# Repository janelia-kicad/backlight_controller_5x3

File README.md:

- [Repository Information](#orge3a2ecc)
  - [Description](#org1a124a6)
- [Images](#orgde4a8eb)
- [Schematic](#org565d04b)
- [Gerbers](#orgdefb019)
- [Bill of Materials](#orgbfc12b0)
  - [PCB Parts](#org35e0f28)
  - [Supplemental Parts](#orgb5c14fe)
  - [Vendor Parts Lists](#org5ae73cf)
- [Supplemental Documentation](#orgd3afd80)
  - [Assembly Instructions](#orgc67ada5)
- [Manufacturing Archive](#org51454f0)

# Repository Information

-   **Name:** backlight\_controller\_5x3
-   **Version:** 1.3
-   **License:** Open-Source Hardware
-   **URL:** <https://github.com/janelia-kicad/backlight_controller_5x3>
-   **Author:** Peter Polidoro
-   **Email:** peter@polidoro.io

## Description

This board controls up to four Smart Vision backlights with IR and visible channels plus additional high and low power channel outputs.

# Images

# Schematic

[./schematic/backlight\_controller\_5x3.pdf](./schematic/backlight_controller_5x3.pdf)

# Gerbers

# Bill of Materials

## PCB Parts

| Item | Reference(s)                                                | Quantity | Manufacturer Part Number | Description                                                       |
|---- |----------------------------------------------------------- |-------- |------------------------ |----------------------------------------------------------------- |
| 1    | C1 C2 C3 C4 C5 C6                                           | 6        | C0805T104K5RAL7800       | CAP CER 0.1UF 50V X7R                                             |
| 2    | D1                                                          | 1        | PMEG045V100EPDZ          | DIODE SCHOTTKY 45V 10A                                            |
| 3    | D10 D11 D12 D13 D14 D15 D16 D17 D18 D2 D3 D4 D5 D6 D7 D8 D9 | 17       | LTST-C170GKT             | LED GREEN CLEAR SMD                                               |
| 4    | HPS1 HPS2 HPS3 HPS4                                         | 4        | BTS3256DAUMA1            | IC SWITCH SMART LOWSIDE                                           |
| 5    | J1 J2                                                       | 2        | PBC25SAAN                | CONN HEADER VERT 25POS 2.54MM                                     |
| 6    | J10 J11 J12 J5 J6 J7 J8 J9                                  | 8        | 1411976                  | CONN FMALE INSERT 5POS SOLDER                                     |
| 7    | J3                                                          | 1        | 09551156612741           | CONN D-SUB RCPT 9POS SMD SOLDER                                   |
| 8    | J4                                                          | 1        | 09551296812741           | CONN D-SUB PLUG 9POS SMD SOLDER                                   |
| 9    | P1                                                          | 1        | 0039301060               | CONN HEADER 6POS 4.2MM R/A TIN                                    |
| 10   | R1                                                          | 1        | ERJ-6ENF2201V            | RES SMD 2.2K OHM 1% 1/8W                                          |
| 11   | R10 R12 R14 R16 R18 R19 R2 R20 R21 R22 R23 R24 R25 R4 R6 R8 | 16       | ERJ-6ENF2870V            | RES SMD 287 OHM 1% 1/8W                                           |
| 12   | R11 R13 R15 R17                                             | 4        | ERJ-6ENF75R0V            | RES SMD 75 OHM 1% 1/8W                                            |
| 13   | R3 R5 R7 R9                                                 | 4        | ERJ-6ENF5901V            | RES SMD 5.9K OHM 1% 1/8W                                          |
| 14   | U1 U2                                                       | 2        | SN74ABT541BDWR           | Buffer Non-Inverting 1 Element 8 Bit per Element Push-Pull Output |
| 15   | U10 U3 U4 U5 U6 U7 U8 U9                                    | 8        | NUD3124LT1G              | IC INDCT LOAD DRVR AUTO                                           |

## Supplemental Parts

| Item | Quantity | Manufacturer Part Number   | Description                    |
|---- |-------- |-------------------------- |------------------------------ |
| 1    | 1        | GST280A24-C6P              | AC/DC DESKTOP ADAPTER 24V 280W |
| 2    | 1        | CORD IEC 320-C13 6FT BLACK | CORD IEC 320-C13 6FT BLACK     |

## Vendor Parts Lists

[./bom/Digi-Key\_parts.csv](./bom/Digi-Key_parts.csv)

[./bom/supplemental\_Digi-Key\_parts.csv](./bom/supplemental_Digi-Key_parts.csv)

# Supplemental Documentation

## Assembly Instructions

-   Solder surface mount and through hole components onto the pcb.

# Manufacturing Archive

Send manufacturing zip file to your favorite PCB manufacturer for fabrication.

[./manufacturing/backlight\_controller\_5x3\_v1.3.zip](./manufacturing/backlight_controller_5x3_v1.3.zip)

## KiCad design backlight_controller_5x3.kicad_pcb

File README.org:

# Created 2019-05-20 Mon 15:17
#+OPTIONS: title:nil author:nil email:nil toc:t |:t ^:nil
* Repository Information

- Name :: backlight_controller_5x3
- Version :: 1.3
- License :: Open-Source Hardware
- URL :: https://github.com/janelia-kicad/backlight_controller_5x3
- Author :: Peter Polidoro
- Email :: peter@polidoro.io

** Description

This board controls up to four Smart Vision backlights with IR and visible
channels plus additional high and low power channel outputs.

* Images

[[file:./images/top.png]]

[[file:./images/bottom.png]]

* Schematic

[[file:./schematic/backlight_controller_5x3.pdf][./schematic/backlight_controller_5x3.pdf]]

[[file:./schematic/images/schematic00.png]]

[[file:./schematic/images/schematic01.png]]

[[file:./schematic/images/schematic02.png]]

[[file:./schematic/images/schematic03.png]]

[[file:./schematic/images/schematic04.png]]

[[file:./schematic/images/schematic05.png]]

[[file:./schematic/images/schematic06.png]]

[[file:./schematic/images/schematic07.png]]

[[file:./schematic/images/schematic08.png]]

[[file:./schematic/images/schematic09.png]]

[[file:./schematic/images/schematic10.png]]

[[file:./schematic/images/schematic11.png]]

[[file:./schematic/images/schematic12.png]]

[[file:./schematic/images/schematic13.png]]

[[file:./schematic/images/schematic14.png]]

[[file:./schematic/images/schematic15.png]]

[[file:./schematic/images/schematic16.png]]

[[file:./schematic/images/schematic17.png]]

[[file:./schematic/images/schematic18.png]]

[[file:./schematic/images/schematic19.png]]

[[file:./schematic/images/schematic20.png]]

[[file:./schematic/images/schematic21.png]]

* Gerbers

[[file:./gerbers/images/gerbers00.png]]

[[file:./gerbers/images/gerbers01.png]]

* Bill of Materials

** PCB Parts

| Item | Reference(s)                                                | Quantity | Manufacturer Part Number | Description                                                       |
|------+-------------------------------------------------------------+----------+--------------------------+-------------------------------------------------------------------|
|    1 | C1 C2 C3 C4 C5 C6                                           |        6 | C0805T104K5RAL7800       | CAP CER 0.1UF 50V X7R                                             |
|    2 | D1                                                          |        1 | PMEG045V100EPDZ          | DIODE SCHOTTKY 45V 10A                                            |
|    3 | D10 D11 D12 D13 D14 D15 D16 D17 D18 D2 D3 D4 D5 D6 D7 D8 D9 |       17 | LTST-C170GKT             | LED GREEN CLEAR SMD                                               |
|    4 | HPS1 HPS2 HPS3 HPS4                                         |        4 | BTS3256DAUMA1            | IC SWITCH SMART LOWSIDE                                           |
|    5 | J1 J2                                                       |        2 | PBC25SAAN                | CONN HEADER VERT 25POS 2.54MM                                     |
|    6 | J10 J11 J12 J5 J6 J7 J8 J9                                  |        8 | 1411976                  | CONN FMALE INSERT 5POS SOLDER                                     |
|    7 | J3                                                          |        1 | 09551156612741           | CONN D-SUB RCPT 9POS SMD SOLDER                                   |
|    8 | J4                                                          |        1 | 09551296812741           | CONN D-SUB PLUG 9POS SMD SOLDER                                   |
|    9 | P1                                                          |        1 | 0039301060               | CONN HEADER 6POS 4.2MM R/A TIN                                    |
|   10 | R1                                                          |        1 | ERJ-6ENF2201V            | RES SMD 2.2K OHM 1% 1/8W                                          |
|   11 | R10 R12 R14 R16 R18 R19 R2 R20 R21 R22 R23 R24 R25 R4 R6 R8 |       16 | ERJ-6ENF2870V            | RES SMD 287 OHM 1% 1/8W                                           |
|   12 | R11 R13 R15 R17                                             |        4 | ERJ-6ENF75R0V            | RES SMD 75 OHM 1% 1/8W                                            |
|   13 | R3 R5 R7 R9                                                 |        4 | ERJ-6ENF5901V            | RES SMD 5.9K OHM 1% 1/8W                                          |
|   14 | U1 U2                                                       |        2 | SN74ABT541BDWR           | Buffer Non-Inverting 1 Element 8 Bit per Element Push-Pull Output |
|   15 | U10 U3 U4 U5 U6 U7 U8 U9                                    |        8 | NUD3124LT1G              | IC INDCT LOAD DRVR AUTO                                           |

** Supplemental Parts

| Item | Quantity | Manufacturer Part Number   | Description                    |
|------+----------+----------------------------+--------------------------------|
|    1 |        1 | GST280A24-C6P              | AC/DC DESKTOP ADAPTER 24V 280W |
|    2 |        1 | CORD IEC 320-C13 6FT BLACK | CORD IEC 320-C13 6FT BLACK     |

** Vendor Parts Lists

[[file:./bom/Digi-Key_parts.csv][./bom/Digi-Key_parts.csv]]

[[file:./bom/supplemental_Digi-Key_parts.csv][./bom/supplemental_Digi-Key_parts.csv]]

* Supplemental Documentation

** Assembly Instructions

- Solder surface mount and through hole components onto the pcb.

* Manufacturing Archive

Send manufacturing zip file to your favorite PCB manufacturer for fabrication.

[[file:./manufacturing/backlight_controller_5x3_v1.3.zip][./manufacturing/backlight_controller_5x3_v1.3.zip]]

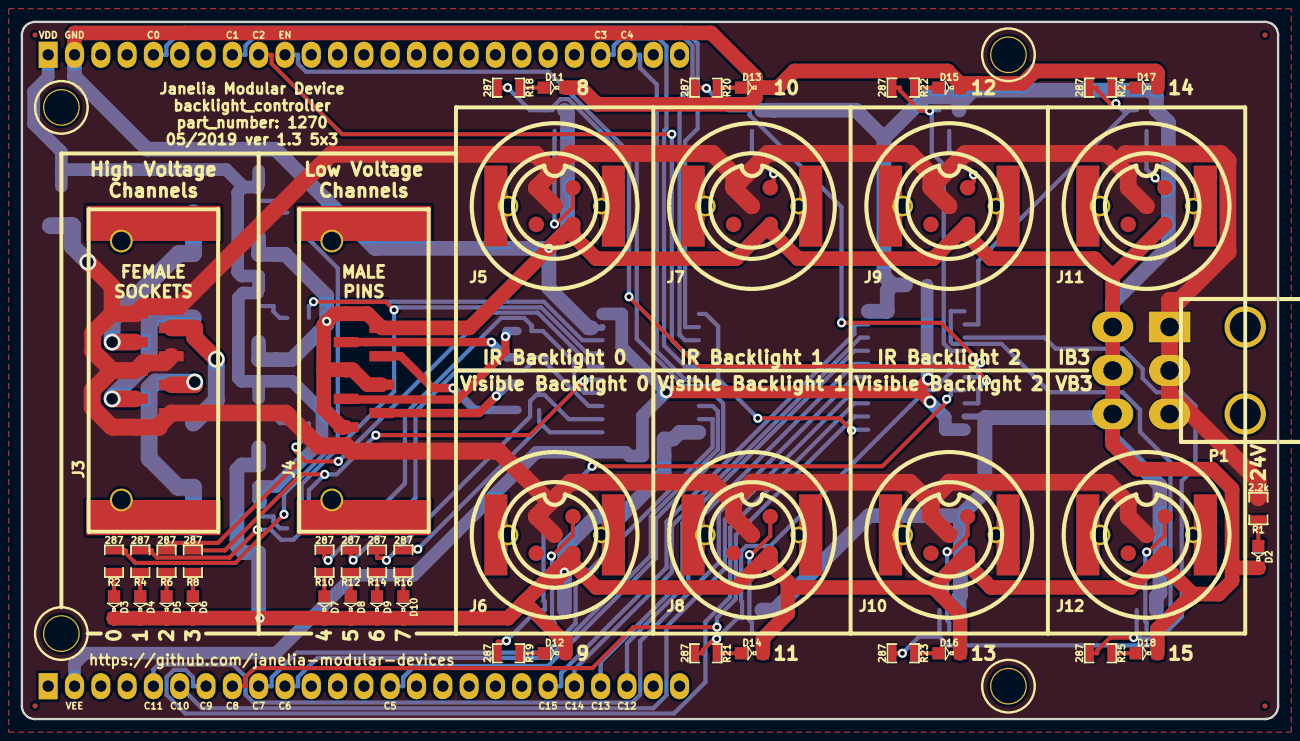
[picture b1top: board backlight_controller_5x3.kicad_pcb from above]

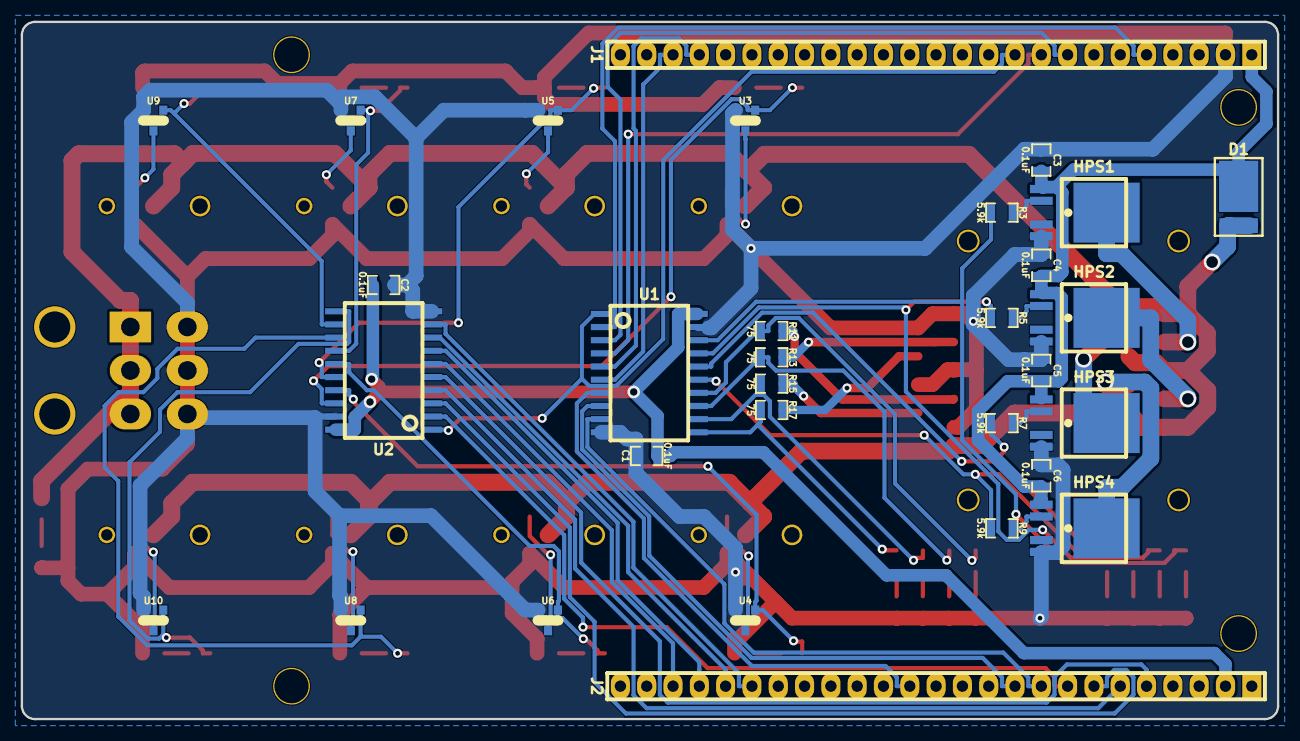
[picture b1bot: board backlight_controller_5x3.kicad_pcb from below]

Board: 2 copper layers, 121.3 x 67.3 mm, 84 parts (31 on the bottom side), 74 nets.

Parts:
C1, C2, C3, C4, C5, C6: 0.1uF; SM0805
D1: DIODE_10A; CFP15
D2, D3, D4, D5, D6, D7, D8, D9, D10, D11, D12, D13, D14, D15, D16, D17, D18: LED_GRN; LED0805
FID1, FID2, FID3, FID4: FIDUCIAL
HPS1, HPS2, HPS3, HPS4: BTS3256; PG-TO252-5-11
J1, J2: HEADER_01X25_MALE; HEADER_01x25
J3: DB9F; DB9F_SMD
J4: DB9M; DB9M_SMD
J5, J6, J7, J8, J9, J10, J11, J12: M12-5-RCPT; M12-5_RCPT_F_SMD
MH1, MH2, MH3, MH4: MOUNTING_HOLE_4-40
P1: MINI_FIT; MINI-FIT-JR_02X03_M_RA
R1: 2.2k; SM0805
R2, R4, R6, R8, R10, R12, R14, R16, R18, R19, R20, R21, R22, R23, R24, R25: 287; SM0805
R3, R5, R7, R9: 5.9k; SM0805
R11, R13, R15, R17: 75; SM0805
U1, U2: SN74ABT541BDWR; SOIC_20
U3, U4, U5, U6, U7, U8, U9, U10: NUD3124; TO-236-3

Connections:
/CHANNEL_0: J1.5, U1.2
/CHANNEL_1: J1.8, U1.3
/CHANNEL_2: J1.9, U1.4
/CHANNEL_3: J1.22, U1.5
/CHANNEL_4: J1.23, U1.6
/CHANNEL_5: J2.14, U1.7
/CHANNEL_6: J2.10, U1.8
/CHANNEL_7: J2.9, U1.9
/CHANNEL_8: J2.8, U2.2
/CHANNEL_9: J2.7, U2.3
/CHANNEL_10: J2.6, U2.4
/CHANNEL_11: J2.5, U2.5
/CHANNEL_12: J2.23, U2.6
/CHANNEL_13: J2.22, U2.7
/CHANNEL_14: J2.21, U2.8
/CHANNEL_15: J2.20, U2.9
/backlight_5x3/C_0: R2.1, R3.1, U1.18
/backlight_5x3/C_1: R4.1, R5.1, U1.17
/backlight_5x3/C_2: R6.1, R7.1, U1.16
/backlight_5x3/C_3: R8.1, R9.1, U1.15
/backlight_5x3/C_4: R10.1, R11.1, U1.14
/backlight_5x3/C_5: R12.1, R13.1, U1.13
/backlight_5x3/C_6: R14.1, R15.1, U1.12
/backlight_5x3/C_7: R16.1, R17.1, U1.11
/backlight_5x3/C_8: R18.1, U2.18, U3.1
/backlight_5x3/C_9: R19.1, U2.17, U4.1
/backlight_5x3/C_10: R20.1, U2.16, U5.1
/backlight_5x3/C_11: R21.1, U2.15, U6.1
/backlight_5x3/C_12: R22.1, U2.14, U7.1
/backlight_5x3/C_13: R23.1, U2.13, U8.1
/backlight_5x3/C_14: R24.1, U2.12, U9.1
/backlight_5x3/C_15: R25.1, U2.11, U10.1
/backlight_5x3/backlight_outputs/ir_0/NPN: J5.2, U3.3
/backlight_5x3/backlight_outputs/ir_1/NPN: J7.2, U5.3
/backlight_5x3/backlight_outputs/ir_2/NPN: J9.2, U7.3
/backlight_5x3/backlight_outputs/ir_3/NPN: J11.2, U9.3
/backlight_5x3/backlight_outputs/visible_0/NPN: J6.2, U4.3
/backlight_5x3/backlight_outputs/visible_1/NPN: J8.2, U6.3
/backlight_5x3/backlight_outputs/visible_2/NPN: J10.2, U8.3
/backlight_5x3/backlight_outputs/visible_3/NPN: J12.2, U10.3
/backlight_5x3/high_voltage_outputs/OUTPUT_0: HPS1.6, J3.2
/backlight_5x3/high_voltage_outputs/OUTPUT_1: HPS2.6, J3.4
/backlight_5x3/high_voltage_outputs/OUTPUT_2: HPS3.6, J3.6
/backlight_5x3/high_voltage_outputs/OUTPUT_3: HPS4.6, J3.8
/backlight_5x3/high_voltage_outputs/high_voltage_output_0/FAULT: HPS1.2, R3.2
/backlight_5x3/high_voltage_outputs/high_voltage_output_1/FAULT: HPS2.2, R5.2
/backlight_5x3/high_voltage_outputs/high_voltage_output_2/FAULT: HPS3.2, R7.2
/backlight_5x3/high_voltage_outputs/high_voltage_output_3/FAULT: HPS4.2, R9.2
/backlight_5x3/low_voltage_outputs/OUTPUT_0: J4.2, R11.2
/backlight_5x3/low_voltage_outputs/OUTPUT_1: J4.4, R13.2
/backlight_5x3/low_voltage_outputs/OUTPUT_2: J4.6, R15.2
/backlight_5x3/low_voltage_outputs/OUTPUT_3: J4.8, R17.2
/~ENABLE: J1.10, U1.1, U2.1
GND: C1.2, C2.2, C3.2, C4.2, C5.2, C6.2, D2.2, D3.2, D4.2, D5.2, D6.2, D7.2, D8.2, D9.2, D10.2, D11.2, D12.2, D13.2, D14.2, D15.2, D16.2, D17.2, D18.2, HPS1.5, HPS2.5, HPS3.5, HPS4.5, J1.2, J4.1, J4.3, J4.5, J4.7, J4.9, J5.3, J6.3, J7.3, J8.3, J9.3, J10.3, J11.3, J12.3, P1.4, P1.5, P1.6, U1.10, U1.19, U2.10, U2.19, U3.2, U4.2, U5.2, U6.2, U7.2, U8.2, U9.2, U10.2
unnamed: D2.1, R1.2
unnamed: D3.1, R2.2
unnamed: D4.1, R4.2
unnamed: D5.1, R6.2
unnamed: D6.1, R8.2
unnamed: D7.1, R10.2
unnamed: D8.1, R12.2
unnamed: D9.1, R14.2
unnamed: D10.1, R16.2
unnamed: D11.1, R18.2
unnamed: D12.1, R19.2
unnamed: D13.1, R20.2
unnamed: D14.1, R21.2
unnamed: D15.1, R22.2
unnamed: D16.1, R23.2
unnamed: D17.1, R24.2
unnamed: D18.1, R25.2
VAA: D1.2, J3.1, J3.3, J3.5, J3.7, J3.9, J5.1, J5.5, J6.1, J6.5, J7.1, J7.5, J8.1, J8.5, J9.1, J9.5, J10.1, J10.5, J11.1, J11.5, J12.1, J12.5, P1.1, P1.2, P1.3, R1.1
VDD: C3.1, C4.1, C5.1, C6.1, D1.1, HPS1.1, HPS2.1, HPS3.1, HPS4.1, J1.1
VEE: C1.1, C2.1, J2.2, U1.20, U2.20

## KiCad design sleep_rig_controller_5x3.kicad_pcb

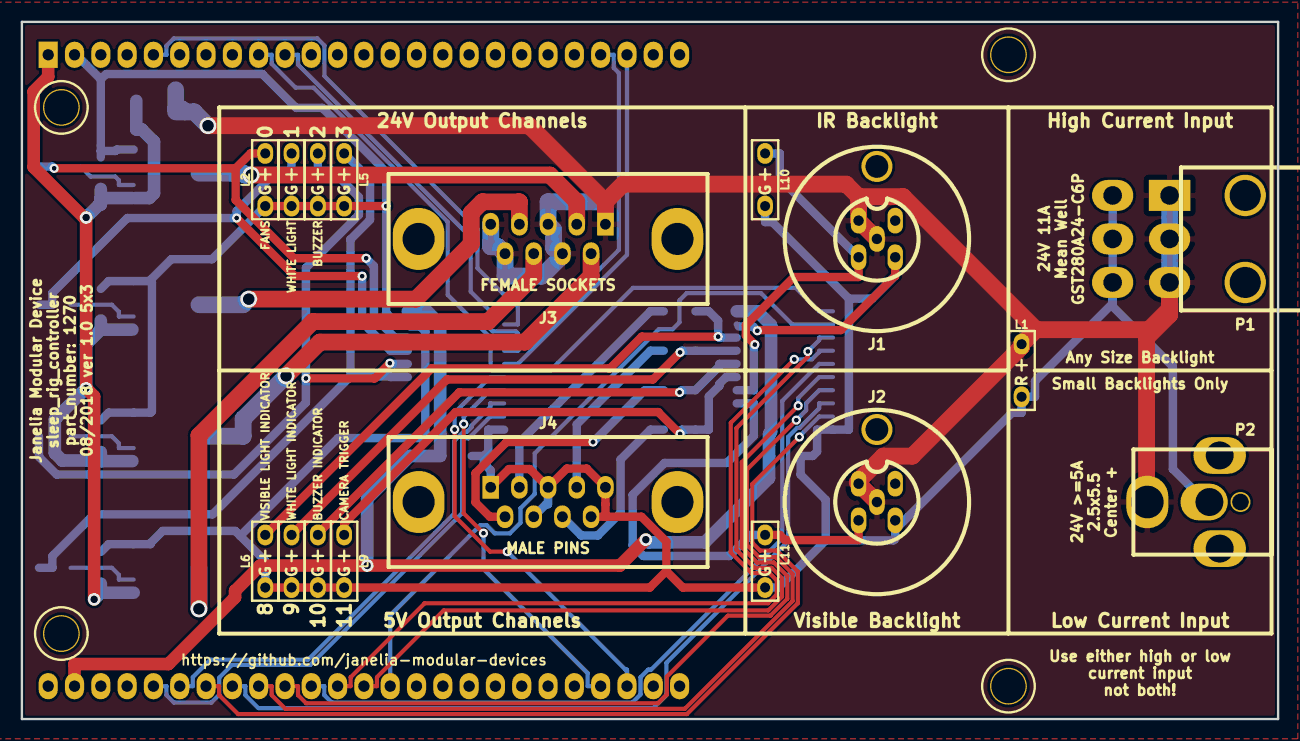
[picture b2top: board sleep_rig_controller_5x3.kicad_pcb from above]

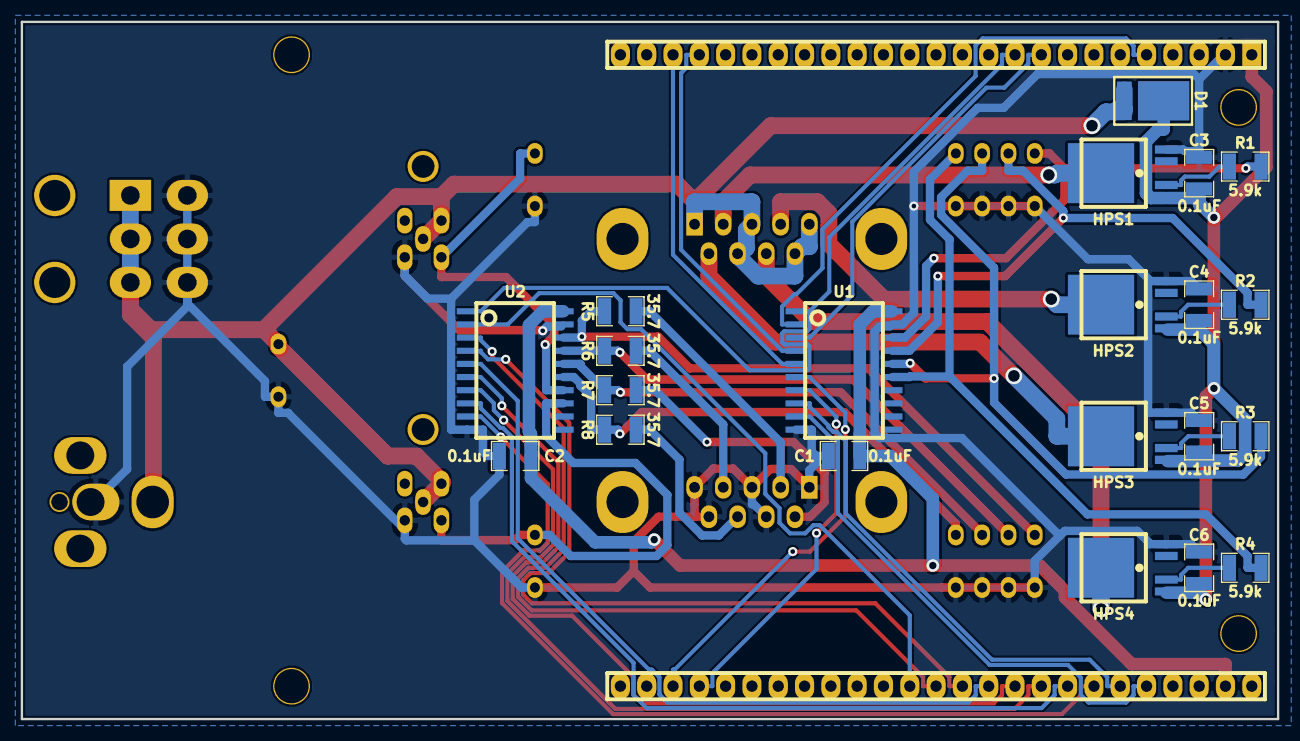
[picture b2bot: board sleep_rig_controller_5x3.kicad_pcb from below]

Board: 2 copper layers, 121.3 x 67.3 mm, 39 parts (21 on the bottom side), 43 nets.

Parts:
C1, C2, C3, C4, C5, C6: 0.1uF; SM1210
D1: diode_schottky_45V_10A; CFP15
HPS1, HPS2, HPS3, HPS4: BTS3256; PG-TO252-5-11
J1, J2: M12-5_RCPT_F
J3: DB9F
J4: DB9M
L1: LED_24V_RED; LED_555-3XXX_R
L2, L3, L4, L5, L6, L7, L8, L9, L10, L11: LED_5V_GRN; LED_555-3XXX_G
MDB1: MODULAR_DEVICE_BASE_5x3_MALE; MODULAR_DEVICE_BASE_5X3_MALE
P1: MINI_FIT_JR_02X03_M_RA; MINI-FIT-JR_02X03_M_RA
P2: PWR_JACK_2.5x5.5; DCJACK_2PIN_HIGHCURRENT
R1, R2, R3, R4: 5.9k; SM1210
R5, R6, R7, R8: 35.7; SM1210
U1, U2: SN74ABT541BDWR; SOIC_20

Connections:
/BUZZER: HPS3.6, J3.6
/BUZZER_INDICATOR: J4.6, R7.1
/CAMERA_TRIGGER: J4.8, R8.1
/CHANNEL_0: MDB1.2, U1.2
/CHANNEL_1: MDB1.6, U1.3
/CHANNEL_2: MDB1.29, U1.4
/CHANNEL_3: MDB1.30, U1.5
/CHANNEL_4: MDB1.35, U1.6
/CHANNEL_5: MDB1.36, U1.7
/CHANNEL_6: MDB1.22, U1.8
/CHANNEL_7: MDB1.23, U1.9
/CHANNEL_8: MDB1.14, U2.2
/CHANNEL_9: MDB1.15, U2.3
/CHANNEL_10: MDB1.16, U2.4
/CHANNEL_11: MDB1.17, U2.5
/CHANNEL_12: MDB1.18, U2.6
/CHANNEL_13: MDB1.19, U2.7
/CHANNEL_14: MDB1.20, U2.8
/CHANNEL_15: MDB1.21, U2.9
/C_0: L2.1, R1.2, U1.18
/C_1: L3.1, R2.2, U1.17
/C_2: L4.1, R3.2, U1.16
/C_3: L5.1, R4.2, U1.15
/C_8: L6.1, R5.2, U2.18
/C_9: L7.1, R6.2, U2.17
/C_10: L8.1, R7.2, U2.16
/C_11: L9.1, R8.2, U2.15
/C_12: J1.4, L10.1, U2.14
/C_13: J2.4, L11.1, U2.13
/FANS: HPS1.6, J3.2
/OUTPUT_3: HPS4.6, J3.8
/VISIBLE_LIGHT_INDICATOR: J4.2, R5.1
/WHITE_LIGHT: HPS2.6, J3.4
/WHITE_LIGHT_INDICATOR: J4.4, R6.1
/output_0/FAULT: HPS1.2, R1.1
/output_1/FAULT: HPS2.2, R2.1
/output_2/FAULT: HPS3.2, R3.1
/output_3/FAULT: HPS4.2, R4.1
/~ENABLE: MDB1.52, U1.1, U2.1
GND: C1.2, C2.2, C3.2, C4.2, C5.2, C6.2, HPS1.5, HPS2.5, HPS3.5, HPS4.5, J1.3, J2.3, J4.1, J4.3, J4.5, J4.7, J4.9, L1.2, L2.2, L3.2, L4.2, L5.2, L6.2, L7.2, L8.2, L9.2, L10.2, L11.2, MDB1.GND, P1.4, P1.5, P1.6, P2.2, U1.10, U1.19, U2.10, U2.19
VAA: D1.2, J1.1, J1.5, J2.1, J2.5, J3.1, J3.3, J3.5, J3.7, J3.9, L1.1, P1.1, P1.2, P1.3, P2.1
VDD: C3.1, C4.1, C5.1, C6.1, D1.1, HPS1.1, HPS2.1, HPS3.1, HPS4.1, MDB1.VDD
VEE: C1.1, C2.1, MDB1.VEE, U1.20, U2.20

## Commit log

2018-08-09 Initial commit.
2018-08-09 Added generate_kicad_documentation.
2018-08-09 Added some components and footprints.
2018-08-09 Added DB-9 components.
2018-08-10 Added more parts and partially filled out bom.
2018-08-12 Removed v4 files.
2018-08-22 Updated submodules.
2018-08-23 Partially designed.
2018-08-23 Added digikey_order.
2018-08-23 Added items.
2018-08-23 Added low_power_channels.
2018-08-24 Removed F.SilkS from pads.
2018-08-24 Finished layout of v1.0.
2018-08-27 Finished version 1.0.
2018-08-27 Added some documentation.
2018-08-27 Removed *.SilkS from pads.
2018-08-27 Added 24V led and swapped green led for one in stock.
2018-08-27 Switched back to smaller leds.
2018-08-28 Rerouted traces.
2018-08-28 Added to supplemental bom.
2018-09-10 smart_vision -> sleep_rig.
2018-09-10 Rearranged components.
2018-09-11 More progress towards v1.0.
2018-09-12 sleep_rig -> backlight.
2018-09-12 Reorganized schematics.
2018-09-12 Finished schematic v1.0.
2018-09-12 Initial footprint layout.
2018-09-12 Another schematic reorganization.
2018-09-12 Reorganized schematics, ready to layout traces.
2018-09-12 Added autorouted traces.
2018-09-13 Updated documentation.
2018-09-13 Updated README.
2018-09-13 Updated footprints and components.
2018-09-13 Fixed footprint errors.
2018-10-19 Changes towards v1.1.
2018-10-20 Finished version 1.1.
2018-10-23 Updated version number.
2018-10-23 Updated version 1.1 documentation.
2018-10-26 Updated supplemental bom.
2018-10-29 high_power -> high_voltage. low_power -> low_voltage.
2018-10-29 Progress towards v1.2.
2018-10-29 Finished v1.2 schematic.
2018-10-29 Finished version 1.2.
2018-11-02 Added README.md.
2018-11-05 Added images.
2019-05-09 Prepare for version 1.3
2019-05-09 Remove old components
2019-05-09 Add modular_device_base_5x3_male
2019-05-10 Mfg -> Manufacturer, Supplier -> Vendor, PN -> Part Number
2019-05-10 More progress towards v1.3
2019-05-13 Make modular device base schematic
2019-05-13 Finish schematic v1.3
2019-05-17 Update schematic
2019-05-17 Place footprints
2019-05-17 Update documentation
2019-05-20 Fix missing component field values
2019-05-20 Updated documentation
2021-09-16 Update email address
2021-09-21 Remove ignored files
2022-02-22 Add guix files
2022-02-23 Add guix documentation
